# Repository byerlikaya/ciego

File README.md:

CIEGO

Visual Mystery Systems

The goal of this project is to turn any glass surface (display window, window, car window, etc.) into a screen.

The working principle of the project is to automatically play videos loaded onto the device at specified intervals.

Imagine this: You are in a shopping mall, and suddenly the storefront of the store in front of you turns into a giant screen, playing the brand's campaign videos or advertisements. Isn't it fascinating?

Or consider this: While you are browsing store windows (through sensors that detect you), suddenly the store's window turns into a screen, showing you campaigns related to the products you are looking at.

You can play the videos you want hourly or at intervals you determine.

Or if you are a store owner and want your store to stand out in the evenings, you can deliver your brand's ads or campaigns to your customers when you are not there. Isn't it an effective method, in your opinion?

Of course, there are many technical details in this project that I cannot share here, but I have tried to support it as visually as possible.

The project runs on Raspberry Pi and has been developed using Python.

For a better understanding, here is a video of the project. 👇

https://github.com/byerlikaya/ciego/assets/9534517/c77c7ad7-eaf2-4a72-a40a-bc6bd9213c8d

<b><i>Double-layer circuit design for connection sockets (drawn using KiCad).</i></b>

[ciego.pdf](https://github.com/byerlikaya/ciego/files/12550504/ciego.pdf)

<b><i>Images related to the project</i></b> 🖼️

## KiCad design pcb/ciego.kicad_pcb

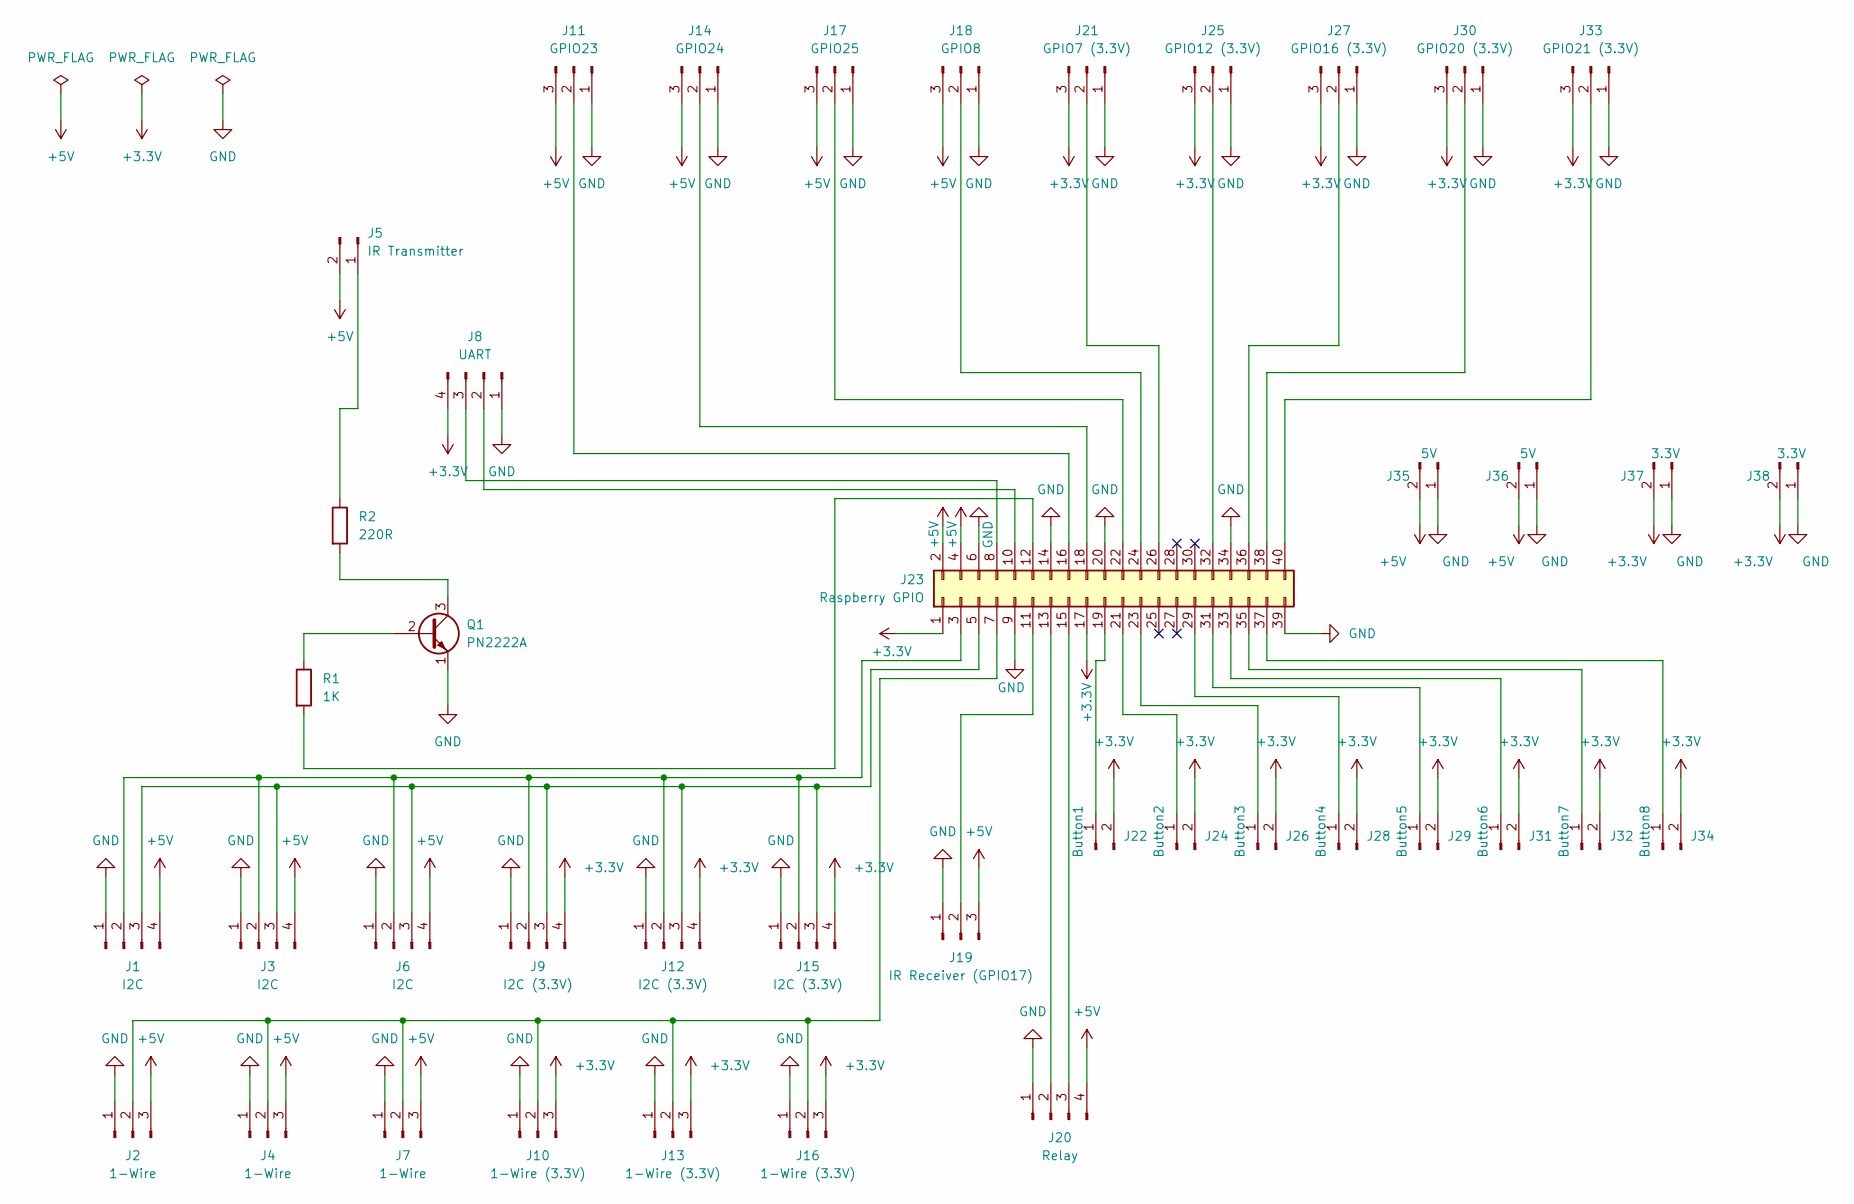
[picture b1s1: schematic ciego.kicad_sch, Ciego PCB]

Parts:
J1, J3, J6: I2C; JST_XH_B4B-XH-A_1x04_P2.50mm_Vertical
J2, J4, J7: 1-Wire; JST_XH_B3B-XH-A_1x03_P2.50mm_Vertical
J5: IR Transmitter; JST_XH_B2B-XH-A_1x02_P2.50mm_Vertical
J8: UART; JST_XH_B4B-XH-A_1x04_P2.50mm_Vertical
J9, J12, J15: I2C (3.3V); JST_XH_B4B-XH-A_1x04_P2.50mm_Vertical
J10, J13, J16: 1-Wire (3.3V); JST_XH_B3B-XH-A_1x03_P2.50mm_Vertical
J11: GPIO23; JST_XH_B3B-XH-A_1x03_P2.50mm_Vertical
J14: GPIO24; JST_XH_B3B-XH-A_1x03_P2.50mm_Vertical
J17: GPIO25; JST_XH_B3B-XH-A_1x03_P2.50mm_Vertical
J18: GPIO8; JST_XH_B3B-XH-A_1x03_P2.50mm_Vertical
J19: IR Receiver (GPIO17); JST_XH_B3B-XH-A_1x03_P2.50mm_Vertical
J20: Relay; JST_XH_B4B-XH-A_1x04_P2.50mm_Vertical
J21: GPIO7 (3.3V); JST_XH_B3B-XH-A_1x03_P2.50mm_Vertical
J22: Button1; JST_XH_B2B-XH-A_1x02_P2.50mm_Vertical
J23: Raspberry GPIO; IDC-Header_2x20_P2.54mm_Vertical
J24: Button2; JST_XH_B2B-XH-A_1x02_P2.50mm_Vertical
J25: GPIO12 (3.3V); JST_XH_B3B-XH-A_1x03_P2.50mm_Vertical
J26: Button3; JST_XH_B2B-XH-A_1x02_P2.50mm_Vertical
J27: GPIO16 (3.3V); JST_XH_B3B-XH-A_1x03_P2.50mm_Vertical
J28: Button4; JST_XH_B2B-XH-A_1x02_P2.50mm_Vertical
J29: Button5; JST_XH_B2B-XH-A_1x02_P2.50mm_Vertical
J30: GPIO20 (3.3V); JST_XH_B3B-XH-A_1x03_P2.50mm_Vertical
J31: Button6; JST_XH_B2B-XH-A_1x02_P2.50mm_Vertical
J32: Button7; JST_XH_B2B-XH-A_1x02_P2.50mm_Vertical
J33: GPIO21 (3.3V); JST_XH_B3B-XH-A_1x03_P2.50mm_Vertical
J34: Button8; JST_XH_B2B-XH-A_1x02_P2.50mm_Vertical
J35, J36: 5V; JST_XH_B2B-XH-A_1x02_P2.50mm_Vertical
J37, J38: 3.3V; JST_XH_B2B-XH-A_1x02_P2.50mm_Vertical
Q1: PN2222A; TO-92_Inline_Wide
R1: 1K; R_Axial_DIN0207_L6.3mm_D2.5mm_P10.16mm_Horizontal
R2: 220R; R_Axial_DIN0207_L6.3mm_D2.5mm_P10.16mm_Horizontal

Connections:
+3.3V: J8.4, J9.4, J10.3, J12.4, J13.3, J15.4, J16.3, J21.3, J22.2, J23.1, J23.17, J24.2, J25.3, J26.2, J27.3, J28.2, J29.2, J30.3, J31.2, J32.2, J33.3, J34.2, J37.2, J38.2
+5V: J1.4, J2.3, J3.4, J4.3, J5.2, J6.4, J7.3, J11.3, J14.3, J17.3, J18.3, J19.3, J20.4, J23.2, J23.4, J35.2, J36.2
GND: J1.1, J2.1, J3.1, J4.1, J6.1, J7.1, J8.1, J9.1, J10.1, J11.1, J12.1, J13.1, J14.1, J15.1, J16.1, J17.1, J18.1, J19.1, J20.1, J21.1, J23.6, J23.9, J23.14, J23.20, J23.34, J23.39, J25.1, J27.1, J30.1, J33.1, J35.1, J36.1, J37.1, J38.1, Q1.1 (E)
unnamed: J1.2, J3.2, J6.2, J9.2, J12.2, J15.2, J23.3
unnamed: J1.3, J3.3, J6.3, J9.3, J12.3, J15.3, J23.5
unnamed: J5.1, R2.1
unnamed: J2.2, J4.2, J7.2, J10.2, J13.2, J16.2, J23.7
unnamed: J11.2, J23.16
unnamed: J14.2, J23.18
unnamed: J17.2, J23.22
unnamed: J18.2, J23.24
unnamed: J19.2, J23.11
unnamed: J20.2, J23.13
unnamed: J20.3, J23.15
unnamed: J21.2, J23.26
unnamed: J22.1, J23.19
unnamed: J8.3, J23.8
unnamed: J8.2, J23.10
unnamed: J23.12, R1.2
unnamed: J23.21, J24.1
unnamed: J23.23, J26.1
unnamed: J23.29, J28.1
unnamed: J23.31, J29.1
unnamed: J23.32, J25.2
unnamed: J23.33, J31.1
unnamed: J23.35, J32.1
unnamed: J23.36, J27.2
unnamed: J23.37, J34.1
unnamed: J23.38, J30.2
unnamed: J23.40, J33.2
unnamed: Q1.2 (B), R1.1
unnamed: Q1.3 (C), R2.2

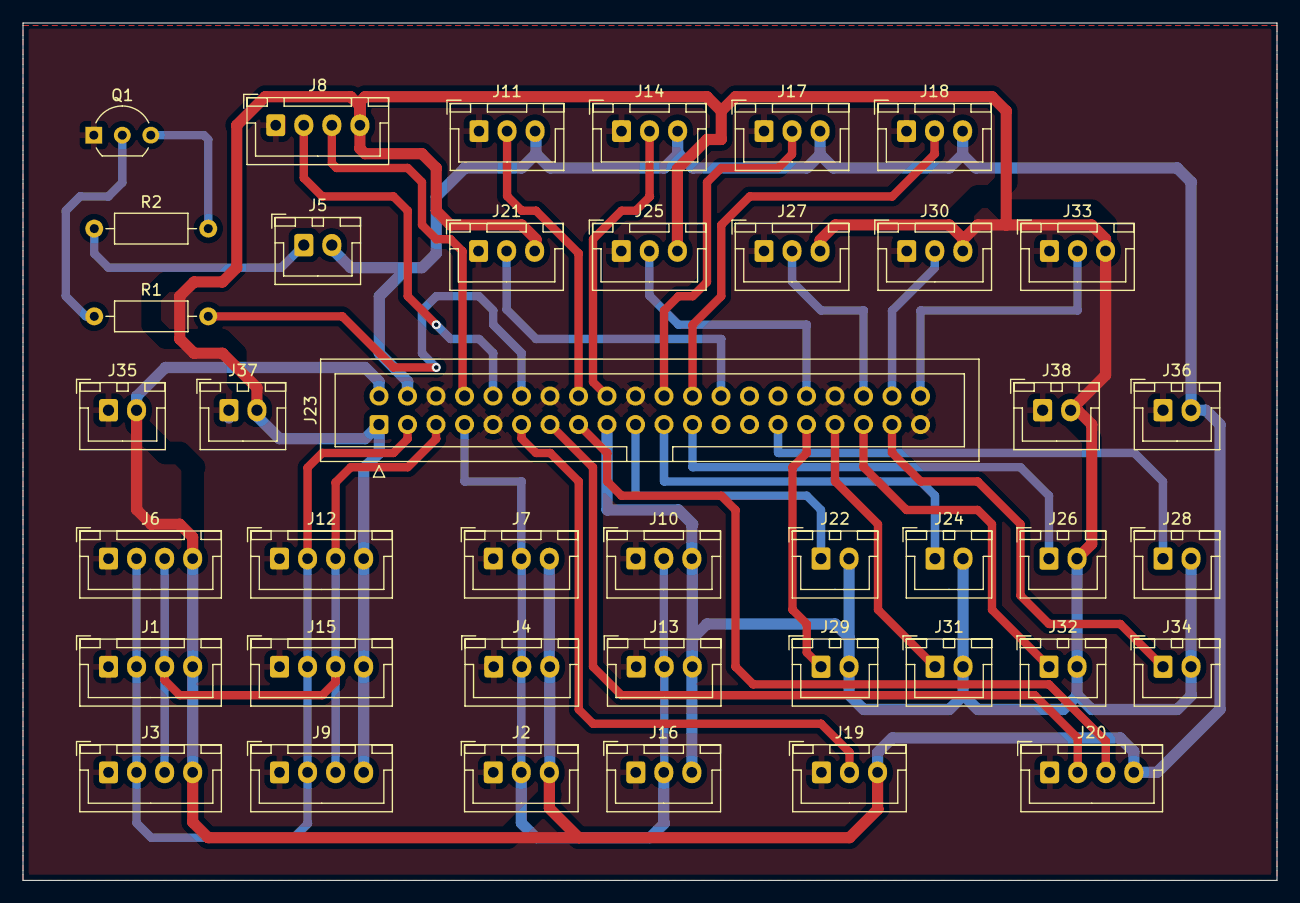
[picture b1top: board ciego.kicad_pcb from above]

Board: 2 copper layers, 111.8 x 76.4 mm, 41 parts (0 on the bottom side), 32 nets.

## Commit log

2023-09-07 Add files via upload
    Project loaded.
2023-09-08 pcb files added.
2023-09-08 Create LICENSE
